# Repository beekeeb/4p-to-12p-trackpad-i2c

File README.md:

# A basic breakout board for the 12p FFC connector

The pins are connected in reverse on purpose. Beware of the trackpad and FFC orientation.

The build log can be found at https://beekeeb.com/cirque-trackpad-i2c-on-corne-keyboard/

## License

This project is licensed under the CERN Open Hardware Licence Version 2 - Permissive (CERN-OHL-P v2). The KiCad symbols and footprints are external projects licensed under the Creative Commons CC-BY-SA 4.0 License.

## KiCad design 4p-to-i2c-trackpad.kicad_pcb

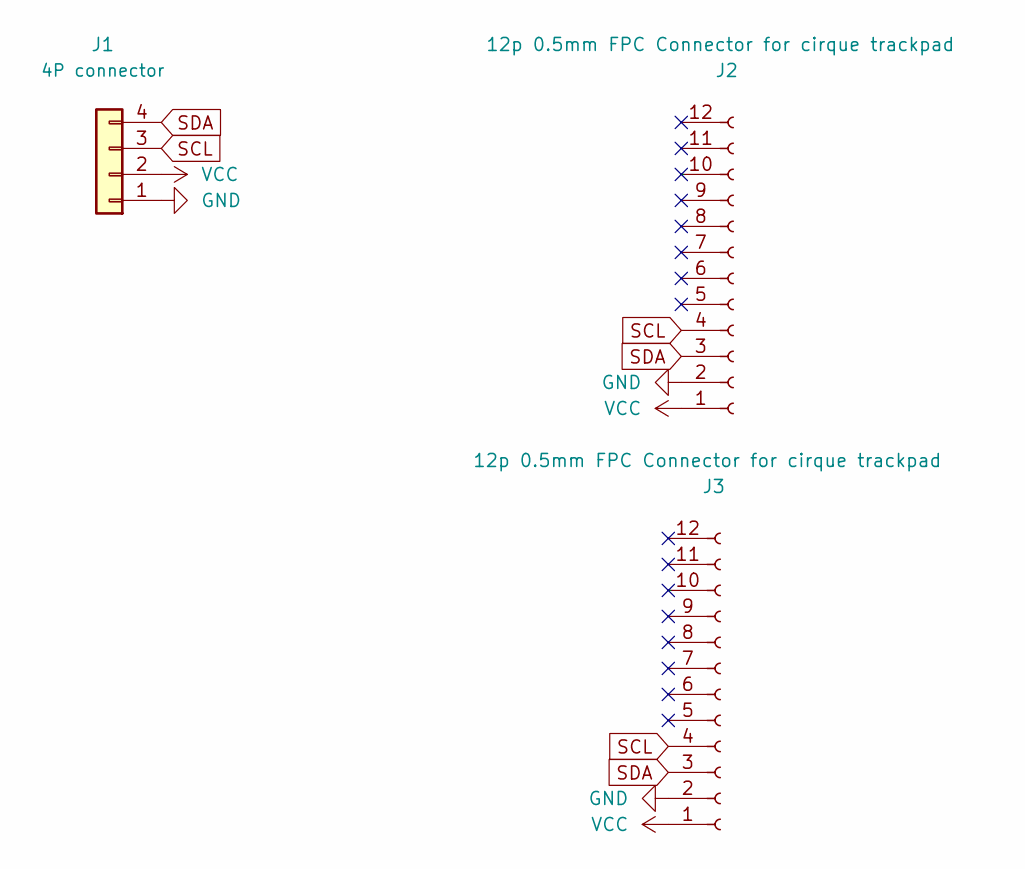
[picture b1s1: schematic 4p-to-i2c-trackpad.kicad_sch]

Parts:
J1: 4P connector; PinHeader_1x04_P2.54mm_Vertical
J2, J3: 12p 0.5mm FPC Connector for cirque trackpad; Hirose_FH12-12S-0.5SH_1x12-1MP_P0.50mm_Horizontal

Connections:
GND: J1.1, J2.2, J3.2
SCL: J1.3, J2.4, J3.4
SDA: J1.4, J2.3, J3.3
VCC: J1.2, J2.1, J3.1

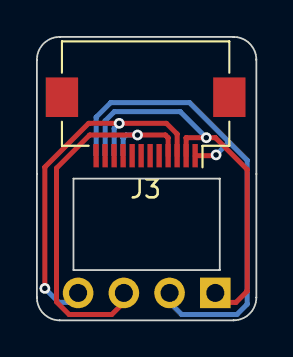
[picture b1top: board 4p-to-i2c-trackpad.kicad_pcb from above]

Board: 2 copper layers, 12.2 x 15.7 mm, 3 parts (1 on the bottom side), 4 nets.
